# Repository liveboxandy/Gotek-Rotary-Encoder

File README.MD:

Initial schematic and gerbers for a Gotek Rotary Encoder PCB.

Used photographs and a multimeter.

Where possible I followed the original PCB routing but Kicad has some different rules for trace widths.

Updated for Kicad 9

Added ibom (bom/ibom.html) Not sure why given the component count.

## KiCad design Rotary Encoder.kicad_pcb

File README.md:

Initial schematic and gerbers for a Gotek Rotary Encoder PCB.

Used photographs and a multimeter.

Where possible I followed the original PCB routing but Kicad has some different rules for trace widths.

Updated for Kicad 9

Added ibom (bom/ibom.html) Not sure why given the component count.

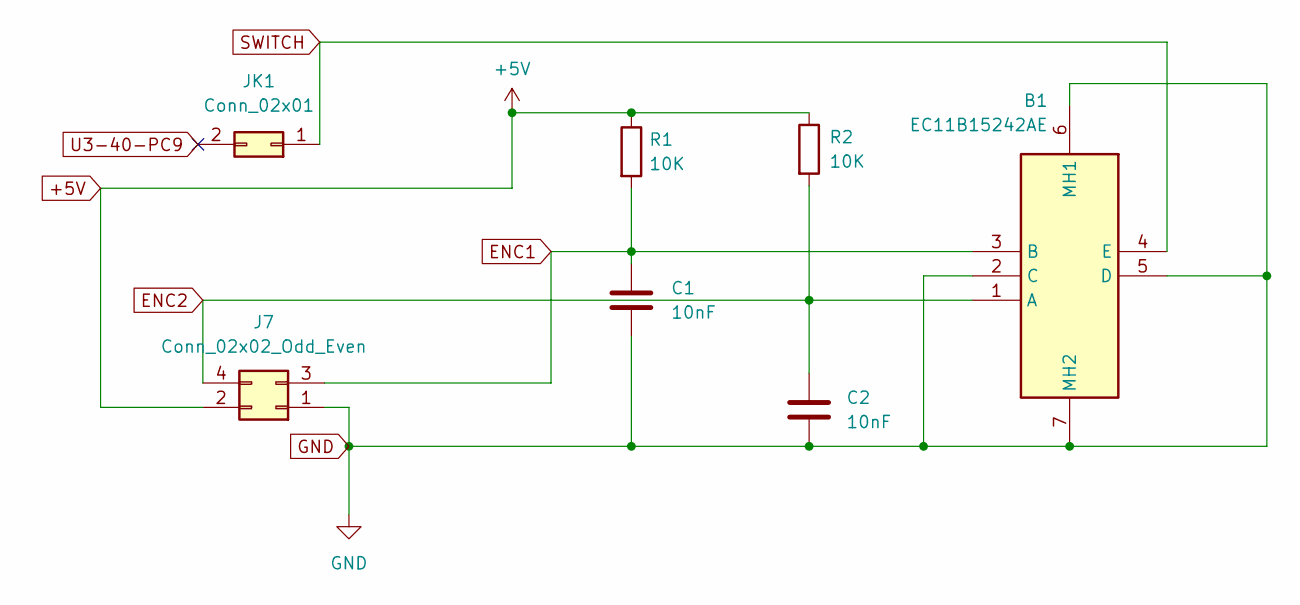
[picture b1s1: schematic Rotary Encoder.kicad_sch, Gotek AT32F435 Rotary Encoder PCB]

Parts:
B1: EC11B15242AE; Manufacturer_Part_Number EC11B15242AE; Mouser Part Number 688-EC11B15242AE
C1, C2: 10nF; C_0805_2012Metric_Pad1.18x1.45mm_HandSolder
J7: Conn_02x02_Odd_Even; PinHeader_2x02_P2.54mm_Horizontal
JK1: Conn_02x01; PinHeader_2x01_P2.54mm_Horizontal
R1, R2: 10K; R_0805_2012Metric_Pad1.20x1.40mm_HandSolder

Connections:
+5V: J7.2, R1.1, R2.1
ENC1: B1.3 (B), C1.1, J7.3, R1.2
ENC2: B1.1 (A), C2.1, J7.4, R2.2
GND: B1.2 (C), B1.5 (D), B1.6 (MH1), B1.7 (MH2), C1.2, C2.2, J7.1
SWITCH: B1.4 (E), JK1.1
U3-40-PC9: JK1.2

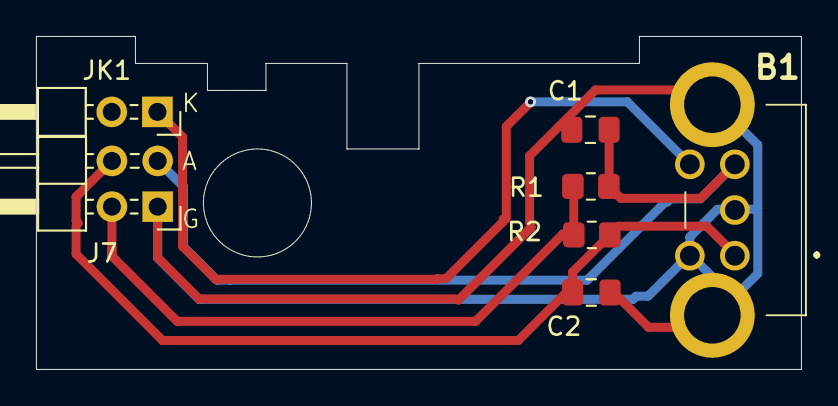
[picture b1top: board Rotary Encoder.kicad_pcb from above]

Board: 2 copper layers, 42.5 x 18.5 mm, 7 parts (0 on the bottom side), 5 nets.

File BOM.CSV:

"Reference","Value","Datasheet","Footprint","Qty","DNP"
"B1","EC11B15242AE","https://www.farnell.com/datasheets/1837001.pdf?_gl=1*s3rpj4*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","Rotary:EC11B15242AE","1",""
"C1,C2","10nF","~","Capacitor_SMD:C_0805_2012Metric_Pad1.18x1.45mm_HandSolder","2",""
"J7","Conn_02x02_Odd_Even","~","Connector_PinHeader_2.54mm:PinHeader_2x02_P2.54mm_Horizontal","1",""
"JK1","Conn_02x01","~","Connector_PinHeader_2.54mm:PinHeader_2x01_P2.54mm_Horizontal","1",""
"R1,R2","10K","~","Resistor_SMD:R_0805_2012Metric_Pad1.20x1.40mm_HandSolder","2",""

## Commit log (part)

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2025-02-19 Add files via upload
    Initial Release
2025-02-20 Add files via upload
    Added labels on schematic and connector pin descriptions to PCB
2025-10-23 Minor Changes
    Updated for Kicad 9
    Added ibom (bom/ibom.html)
